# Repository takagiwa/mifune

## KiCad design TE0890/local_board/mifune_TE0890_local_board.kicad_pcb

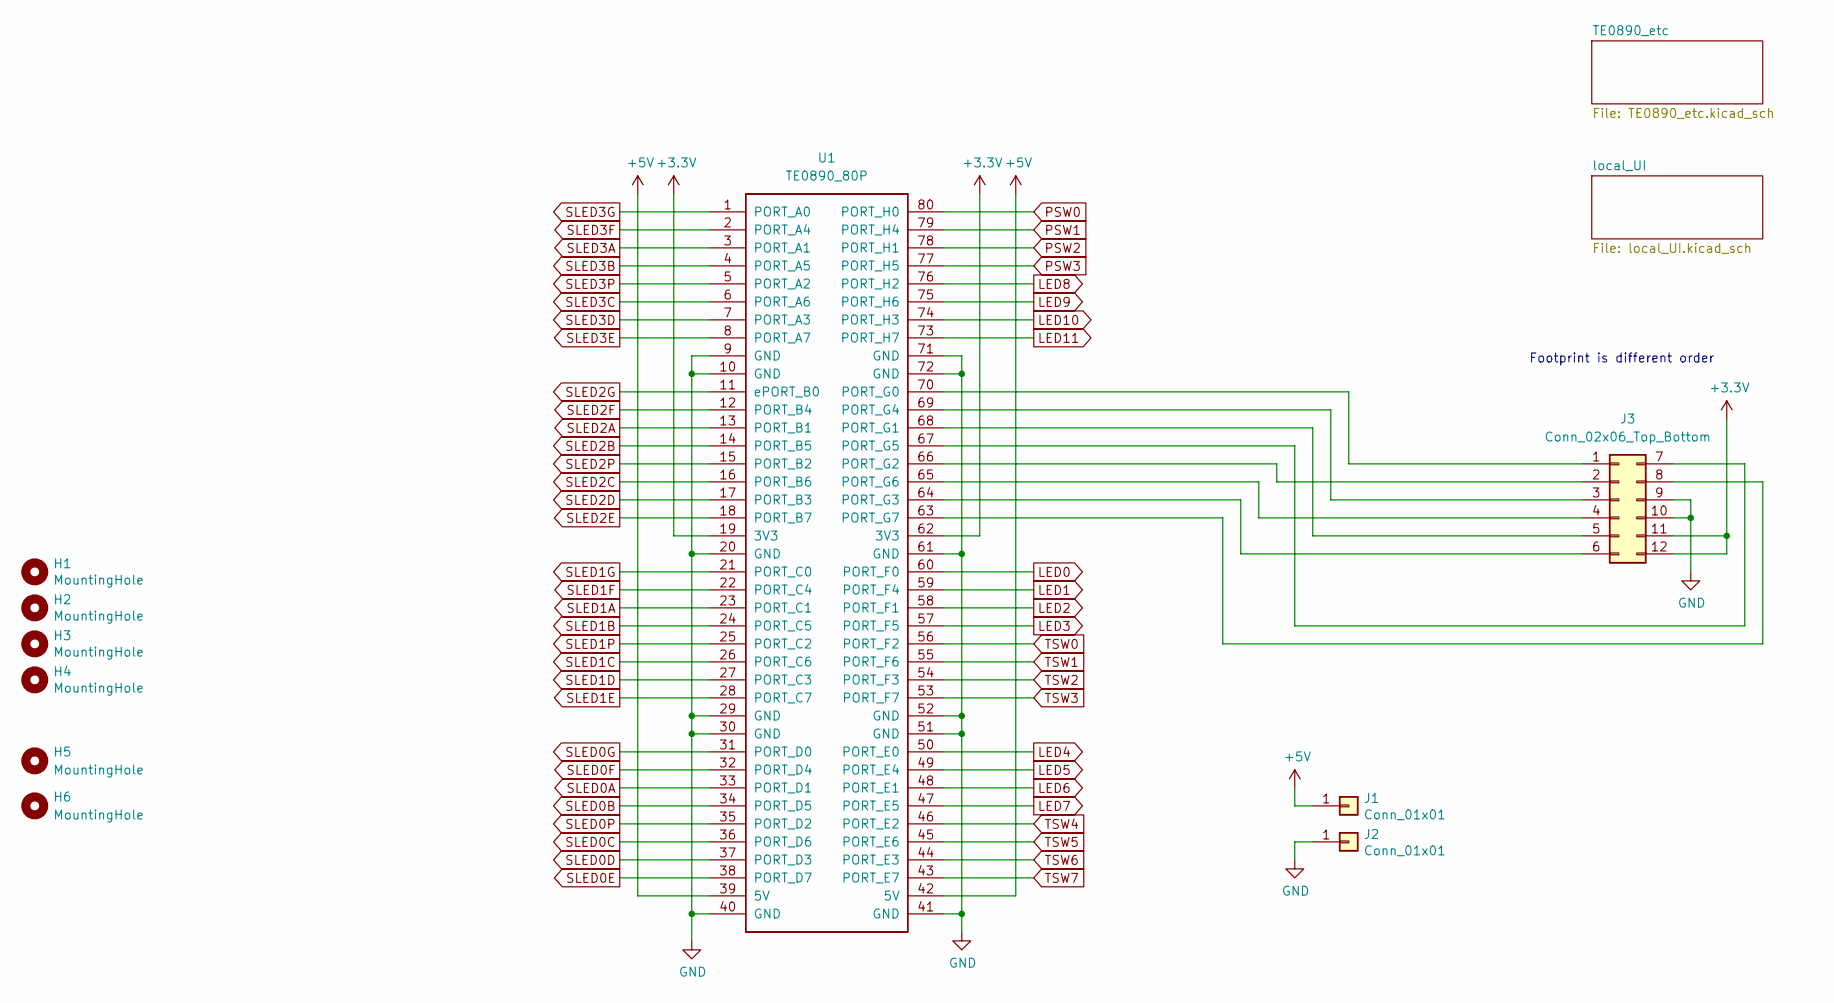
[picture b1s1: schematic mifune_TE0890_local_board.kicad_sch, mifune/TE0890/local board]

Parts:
H1, H2, H3, H4: MountingHole; MountingHole_3.2mm_M3
H5, H6: MountingHole; MountingHole_3.5mm
J1, J2: Conn_01x01; TestPoint_THTPad_D1.5mm_Drill0.7mm
J3: Conn_02x06_Top_Bottom; PinSocket_2x06_P2.54mm_Vertical
U1: TE0890_80P; TE0890_80pin

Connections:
+3V3: J3.11, J3.12, U1.19 (3V3), U1.62 (3V3); also elsewhere on the board
+5V: J1.1, U1.39 (5V), U1.42 (5V); also elsewhere on the board
GND: J2.1, J3.9, J3.10, U1.9 (GND), U1.10 (GND), U1.20 (GND), U1.29 (GND), U1.30 (GND), U1.40 (GND), U1.41 (GND), U1.51 (GND), U1.52 (GND), U1.61 (GND), U1.71 (GND), U1.72 (GND); also elsewhere on the board
LED0: U1.60 (PORT_F0); also elsewhere on the board
LED1: U1.59 (PORT_F4); also elsewhere on the board
LED2: U1.58 (PORT_F1); also elsewhere on the board
LED3: U1.57 (PORT_F5); also elsewhere on the board
LED4: U1.50 (PORT_E0); also elsewhere on the board
LED5: U1.49 (PORT_E4); also elsewhere on the board
LED6: U1.48 (PORT_E1); also elsewhere on the board
LED7: U1.47 (PORT_E5); also elsewhere on the board
LED8: U1.76 (PORT_H2); also elsewhere on the board
LED9: U1.75 (PORT_H6); also elsewhere on the board
LED10: U1.74 (PORT_H3); also elsewhere on the board
LED11: U1.73 (PORT_H7); also elsewhere on the board
unnamed: J3.1, U1.70 (PORT_G0)
unnamed: J3.2, U1.66 (PORT_G2)
unnamed: J3.3, U1.69 (PORT_G4)
unnamed: J3.4, U1.65 (PORT_G6)
unnamed: J3.5, U1.68 (PORT_G1)
unnamed: J3.6, U1.64 (PORT_G3)
unnamed: J3.7, U1.67 (PORT_G5)
unnamed: J3.8, U1.63 (PORT_G7)
PSW0: U1.80 (PORT_H0); also elsewhere on the board
PSW1: U1.79 (PORT_H4); also elsewhere on the board
PSW2: U1.78 (PORT_H1); also elsewhere on the board
PSW3: U1.77 (PORT_H5); also elsewhere on the board
SLED0A: U1.33 (PORT_D1); also elsewhere on the board
SLED0B: U1.34 (PORT_D5); also elsewhere on the board
SLED0C: U1.36 (PORT_D6); also elsewhere on the board
SLED0D: U1.37 (PORT_D3); also elsewhere on the board
SLED0E: U1.38 (PORT_D7); also elsewhere on the board
SLED0F: U1.32 (PORT_D4); also elsewhere on the board
SLED0G: U1.31 (PORT_D0); also elsewhere on the board
SLED0P: U1.35 (PORT_D2); also elsewhere on the board
SLED1A: U1.23 (PORT_C1); also elsewhere on the board
SLED1B: U1.24 (PORT_C5); also elsewhere on the board
SLED1C: U1.26 (PORT_C6); also elsewhere on the board
SLED1D: U1.27 (PORT_C3); also elsewhere on the board
SLED1E: U1.28 (PORT_C7); also elsewhere on the board
SLED1F: U1.22 (PORT_C4); also elsewhere on the board
SLED1G: U1.21 (PORT_C0); also elsewhere on the board
SLED1P: U1.25 (PORT_C2); also elsewhere on the board
SLED2A: U1.13 (PORT_B1); also elsewhere on the board
SLED2B: U1.14 (PORT_B5); also elsewhere on the board
SLED2C: U1.16 (PORT_B6); also elsewhere on the board
SLED2D: U1.17 (PORT_B3); also elsewhere on the board
SLED2E: U1.18 (PORT_B7); also elsewhere on the board
SLED2F: U1.12 (PORT_B4); also elsewhere on the board
SLED2G: U1.11 (ePORT_B0); also elsewhere on the board
SLED2P: U1.15 (PORT_B2); also elsewhere on the board
SLED3A: U1.3 (PORT_A1); also elsewhere on the board
SLED3B: U1.4 (PORT_A5); also elsewhere on the board
SLED3C: U1.6 (PORT_A6); also elsewhere on the board
SLED3D: U1.7 (PORT_A3); also elsewhere on the board
SLED3E: U1.8 (PORT_A7); also elsewhere on the board
SLED3F: U1.2 (PORT_A4); also elsewhere on the board
SLED3G: U1.1 (PORT_A0); also elsewhere on the board
SLED3P: U1.5 (PORT_A2); also elsewhere on the board
TSW0: U1.56 (PORT_F2); also elsewhere on the board
TSW1: U1.55 (PORT_F6); also elsewhere on the board
TSW2: U1.54 (PORT_F3); also elsewhere on the board
TSW3: U1.53 (PORT_F7); also elsewhere on the board
TSW4: U1.46 (PORT_E2); also elsewhere on the board
TSW5: U1.45 (PORT_E6); also elsewhere on the board
TSW6: U1.44 (PORT_E3); also elsewhere on the board
TSW7: U1.43 (PORT_E7); also elsewhere on the board

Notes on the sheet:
Footprint is different order

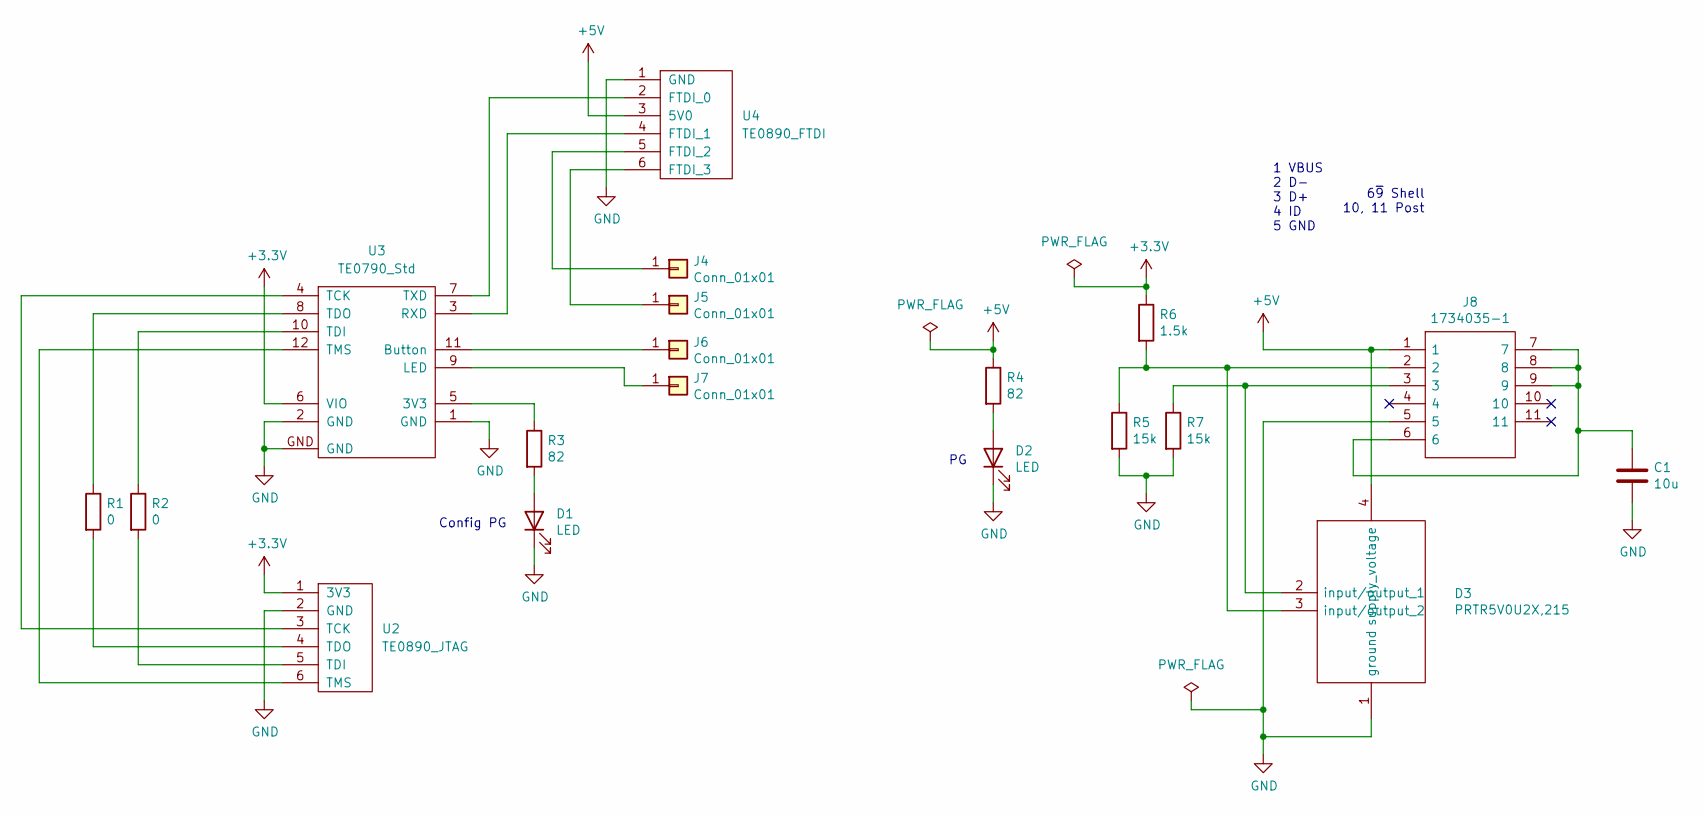
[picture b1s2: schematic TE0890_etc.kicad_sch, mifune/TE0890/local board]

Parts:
C1: 10u; C_0805_2012Metric_Pad1.18x1.45mm_HandSolder
D1, D2: LED; LED_1206_3216Metric_Pad1.42x1.75mm_HandSolder
D3: PRTR5V0U2X,215; PRTR5V0U2X; Mouser Part Number 771-PRTR5V0U2X-T/R
J4, J5, J6, J7: Conn_01x01; TestPoint_THTPad_D2.0mm_Drill1.0mm
J8: 1734035-1; 17340351; Mouser Part Number 571-1734035-1
R1, R2: 0; R_0805_2012Metric_Pad1.20x1.40mm_HandSolder
R3, R4: 82; R_0805_2012Metric_Pad1.20x1.40mm_HandSolder
R5, R7: 15k; R_0805_2012Metric_Pad1.20x1.40mm_HandSolder
R6: 1.5k; R_0805_2012Metric_Pad1.20x1.40mm_HandSolder
U2: TE0890_JTAG; PinHeader_1x06_P2.54mm_Vertical
U3: TE0790_Std; TE0790
U4: TE0890_FTDI; PinHeader_1x06_P2.54mm_Vertical

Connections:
+3V3: R6.1, U2.1 (3V3), U3.6 (VIO); also elsewhere on the board
+5V: D3.4 (supply_voltage), J8.1, R4.1, U4.3 (5V0); also elsewhere on the board
GND: C1.2, D1.1 (K), D2.1 (K), D3.1 (ground), J8.5, R5.2, R7.2, U2.2 (GND), U3.1 (GND), U3.2 (GND), U3.GND, U4.1 (GND); also elsewhere on the board
unnamed: C1.1, J8.6, J8.7, J8.8, J8.9
unnamed: D1.2 (A), R3.2
unnamed: D2.2 (A), R4.2
unnamed: D3.2 (input/output_1), J8.3, R7.1
unnamed: D3.3 (input/output_2), J8.2, R5.1, R6.2
unnamed: J4.1, U4.5 (FTDI_2)
unnamed: J5.1, U4.6 (FTDI_3)
unnamed: J6.1, U3.11 (Button)
unnamed: J7.1, U3.9 (LED)
unnamed: R1.1, U3.8 (TDO)
unnamed: R1.2, U2.4 (TDO)
unnamed: R2.1, U3.10 (TDI)
unnamed: R2.2, U2.5 (TDI)
unnamed: R3.1, U3.5 (3V3)
unnamed: U2.3 (TCK), U3.4 (TCK)
unnamed: U2.6 (TMS), U3.12 (TMS)
unnamed: U3.3 (RXD), U4.4 (FTDI_1)
unnamed: U3.7 (TXD), U4.2 (FTDI_0)

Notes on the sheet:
Config PG
6~{9} Shell 10, 11 Post
1 VBUS 2 D- 3 D+ 4 ID 5 GND

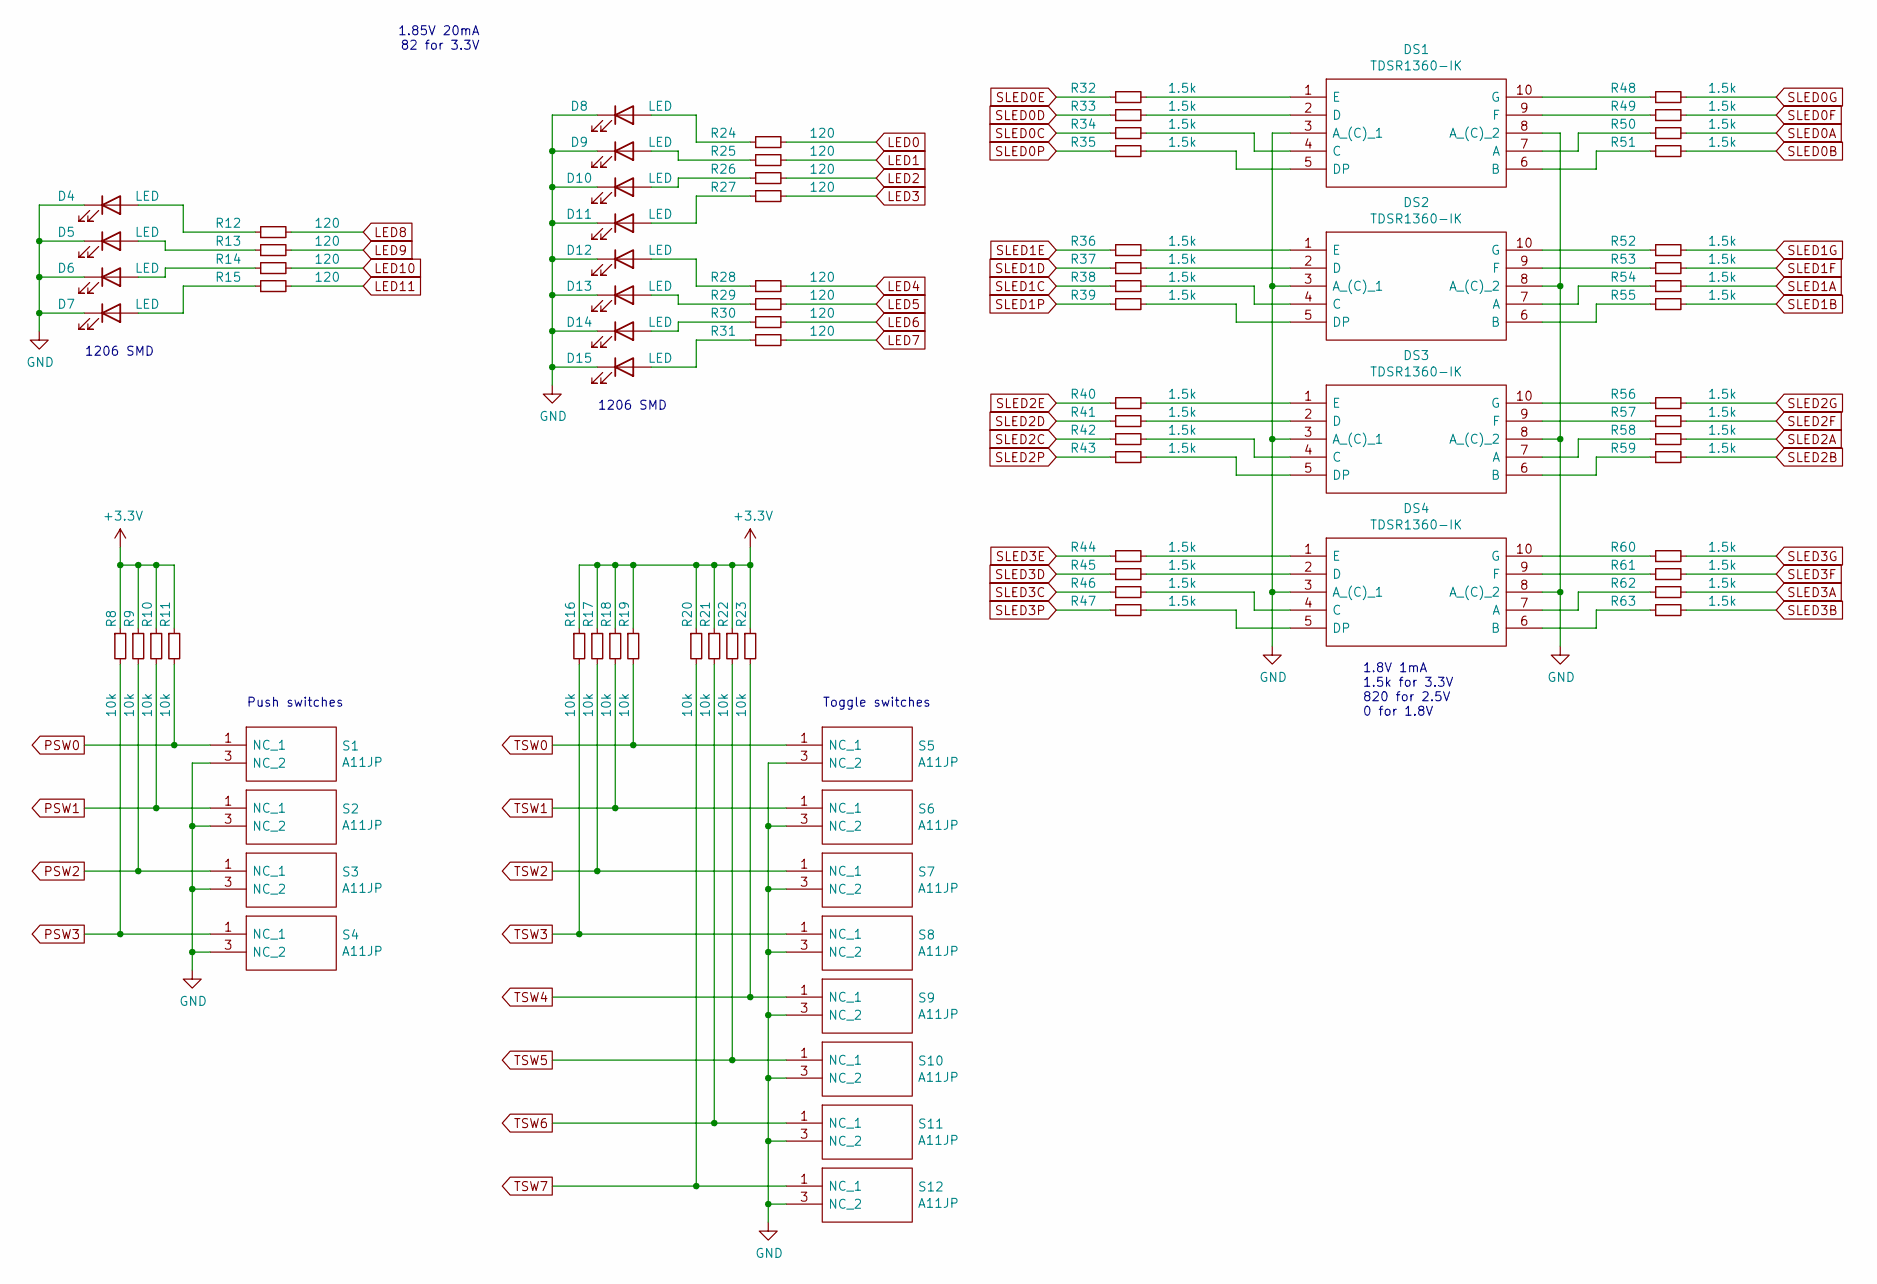
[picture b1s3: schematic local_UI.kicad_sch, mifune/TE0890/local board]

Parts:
D4, D5, D6, D7, D8, D9, D10, D11, D12, D13, D14, D15: LED; LED_1206_3216Metric_Pad1.42x1.75mm_HandSolder
DS1, DS2, DS3, DS4: TDSR1360-IK; TDSR1360IK; Mouser Part Number 78-TDSR1360-IK
R8, R9, R10, R11, R16, R17, R18, R19, R20, R21, R22, R23: 10k; R_0805_2012Metric_Pad1.20x1.40mm_HandSolder
R12, R13, R14, R15, R24, R25, R26, R27, R28, R29, R30, R31: 120; R_0805_2012Metric_Pad1.20x1.40mm_HandSolder
R32, R33, R34, R35, R36, R37, R38, R39, R40, R41, R42, R43, R44, R45, R46, R47, R48, R49, R50, R51, R52, R53, R54, R55, R56, R57, R58, R59, R60, R61, R62, R63: 1.5k; R_0805_2012Metric_Pad1.20x1.40mm_HandSolder
S1, S2, S3, S4, S5, S6, S7, S8, S9, S10, S11, S12: A11JP; Mouser Part Number 633-A11JP

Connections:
+3V3: R8.1, R9.1, R10.1, R11.1, R16.1, R17.1, R18.1, R19.1, R20.1, R21.1, R22.1, R23.1; also elsewhere on the board
GND: D4.1 (K), D5.1 (K), D6.1 (K), D7.1 (K), D8.1 (K), D9.1 (K), D10.1 (K), D11.1 (K), D12.1 (K), D13.1 (K), D14.1 (K), D15.1 (K), DS1.3 (A_(C)_1), DS1.8 (A_(C)_2), DS2.3 (A_(C)_1), DS2.8 (A_(C)_2), DS3.3 (A_(C)_1), DS3.8 (A_(C)_2), DS4.3 (A_(C)_1), DS4.8 (A_(C)_2), S1.3 (NC_2), S2.3 (NC_2), S3.3 (NC_2), S4.3 (NC_2), S5.3 (NC_2), S6.3 (NC_2), S7.3 (NC_2), S8.3 (NC_2), S9.3 (NC_2), S10.3 (NC_2), S11.3 (NC_2), S12.3 (NC_2); also elsewhere on the board
LED0: R24.2; also elsewhere on the board
LED1: R25.2; also elsewhere on the board
LED2: R26.2; also elsewhere on the board
LED3: R27.2; also elsewhere on the board
LED4: R28.2; also elsewhere on the board
LED5: R29.2; also elsewhere on the board
LED6: R30.2; also elsewhere on the board
LED7: R31.2; also elsewhere on the board
LED8: R12.2; also elsewhere on the board
LED9: R13.2; also elsewhere on the board
LED10: R14.2; also elsewhere on the board
LED11: R15.2; also elsewhere on the board
unnamed: D4.2 (A), R12.1
unnamed: D5.2 (A), R13.1
unnamed: D6.2 (A), R14.1
unnamed: D7.2 (A), R15.1
unnamed: D8.2 (A), R24.1
unnamed: D9.2 (A), R25.1
unnamed: D10.2 (A), R26.1
unnamed: D11.2 (A), R27.1
unnamed: D12.2 (A), R28.1
unnamed: D13.2 (A), R29.1
unnamed: D14.2 (A), R30.1
unnamed: D15.2 (A), R31.1
unnamed: DS1.1 (E), R32.2
unnamed: DS1.2 (D), R33.2
unnamed: DS1.4 (C), R34.2
unnamed: DS1.5 (DP), R35.2
unnamed: DS1.6 (B), R51.1
unnamed: DS1.7 (A), R50.1
unnamed: DS1.9 (F), R49.1
unnamed: DS1.10 (G), R48.1
unnamed: DS2.1 (E), R36.2
unnamed: DS2.2 (D), R37.2
unnamed: DS2.4 (C), R38.2
unnamed: DS2.5 (DP), R39.2
unnamed: DS2.6 (B), R55.1
unnamed: DS2.7 (A), R54.1
unnamed: DS2.9 (F), R53.1
unnamed: DS2.10 (G), R52.1
unnamed: DS3.1 (E), R40.2
unnamed: DS3.2 (D), R41.2
unnamed: DS3.4 (C), R42.2
unnamed: DS3.5 (DP), R43.2
unnamed: DS3.6 (B), R59.1
unnamed: DS3.7 (A), R58.1
unnamed: DS3.9 (F), R57.1
unnamed: DS3.10 (G), R56.1
unnamed: DS4.1 (E), R44.2
unnamed: DS4.2 (D), R45.2
unnamed: DS4.4 (C), R46.2
unnamed: DS4.5 (DP), R47.2
unnamed: DS4.6 (B), R63.1
unnamed: DS4.7 (A), R62.1
unnamed: DS4.9 (F), R61.1
unnamed: DS4.10 (G), R60.1
PSW0: R11.2, S1.1 (NC_1); also elsewhere on the board
PSW1: R10.2, S2.1 (NC_1); also elsewhere on the board
PSW2: R9.2, S3.1 (NC_1); also elsewhere on the board
PSW3: R8.2, S4.1 (NC_1); also elsewhere on the board
SLED0A: R50.2; also elsewhere on the board
SLED0B: R51.2; also elsewhere on the board
SLED0C: R34.1; also elsewhere on the board
SLED0D: R33.1; also elsewhere on the board
SLED0E: R32.1; also elsewhere on the board
SLED0F: R49.2; also elsewhere on the board
SLED0G: R48.2; also elsewhere on the board
SLED0P: R35.1; also elsewhere on the board
SLED1A: R54.2; also elsewhere on the board
SLED1B: R55.2; also elsewhere on the board
SLED1C: R38.1; also elsewhere on the board
SLED1D: R37.1; also elsewhere on the board
SLED1E: R36.1; also elsewhere on the board
SLED1F: R53.2; also elsewhere on the board
SLED1G: R52.2; also elsewhere on the board
SLED1P: R39.1; also elsewhere on the board
SLED2A: R58.2; also elsewhere on the board
SLED2B: R59.2; also elsewhere on the board
SLED2C: R42.1; also elsewhere on the board
SLED2D: R41.1; also elsewhere on the board
SLED2E: R40.1; also elsewhere on the board
SLED2F: R57.2; also elsewhere on the board
SLED2G: R56.2; also elsewhere on the board
SLED2P: R43.1; also elsewhere on the board
SLED3A: R62.2; also elsewhere on the board
SLED3B: R63.2; also elsewhere on the board
SLED3C: R46.1; also elsewhere on the board
SLED3D: R45.1; also elsewhere on the board
SLED3E: R44.1; also elsewhere on the board
SLED3F: R61.2; also elsewhere on the board
SLED3G: R60.2; also elsewhere on the board
SLED3P: R47.1; also elsewhere on the board
TSW0: R19.2, S5.1 (NC_1); also elsewhere on the board
TSW1: R18.2, S6.1 (NC_1); also elsewhere on the board
TSW2: R17.2, S7.1 (NC_1); also elsewhere on the board
TSW3: R16.2, S8.1 (NC_1); also elsewhere on the board
TSW4: R23.2, S9.1 (NC_1); also elsewhere on the board
TSW5: R22.2, S10.1 (NC_1); also elsewhere on the board
TSW6: R21.2, S11.1 (NC_1); also elsewhere on the board
TSW7: R20.2, S12.1 (NC_1); also elsewhere on the board

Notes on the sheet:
Toggle switches
1206 SMD
1.8V 1mA 1.5k for 3.3V 820 for 2.5V 0 for 1.8V
Push switches
1.85V 20mA 82 for 3.3V

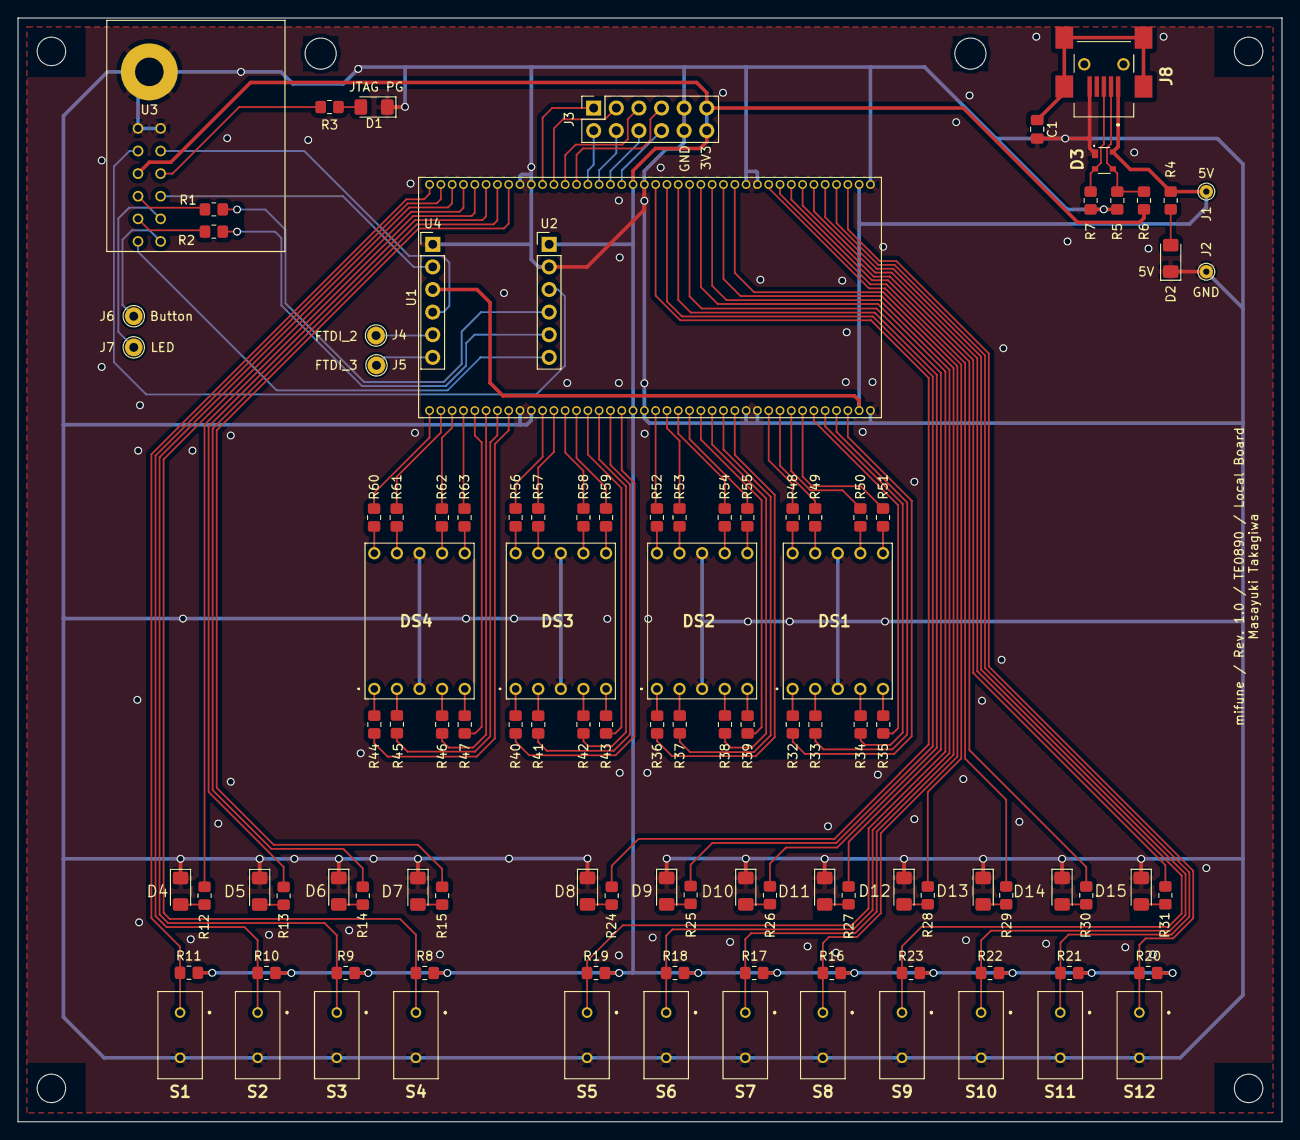
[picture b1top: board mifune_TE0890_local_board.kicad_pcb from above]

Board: 2 copper layers, 142.0 x 124.0 mm, 113 parts (0 on the bottom side), 129 nets.

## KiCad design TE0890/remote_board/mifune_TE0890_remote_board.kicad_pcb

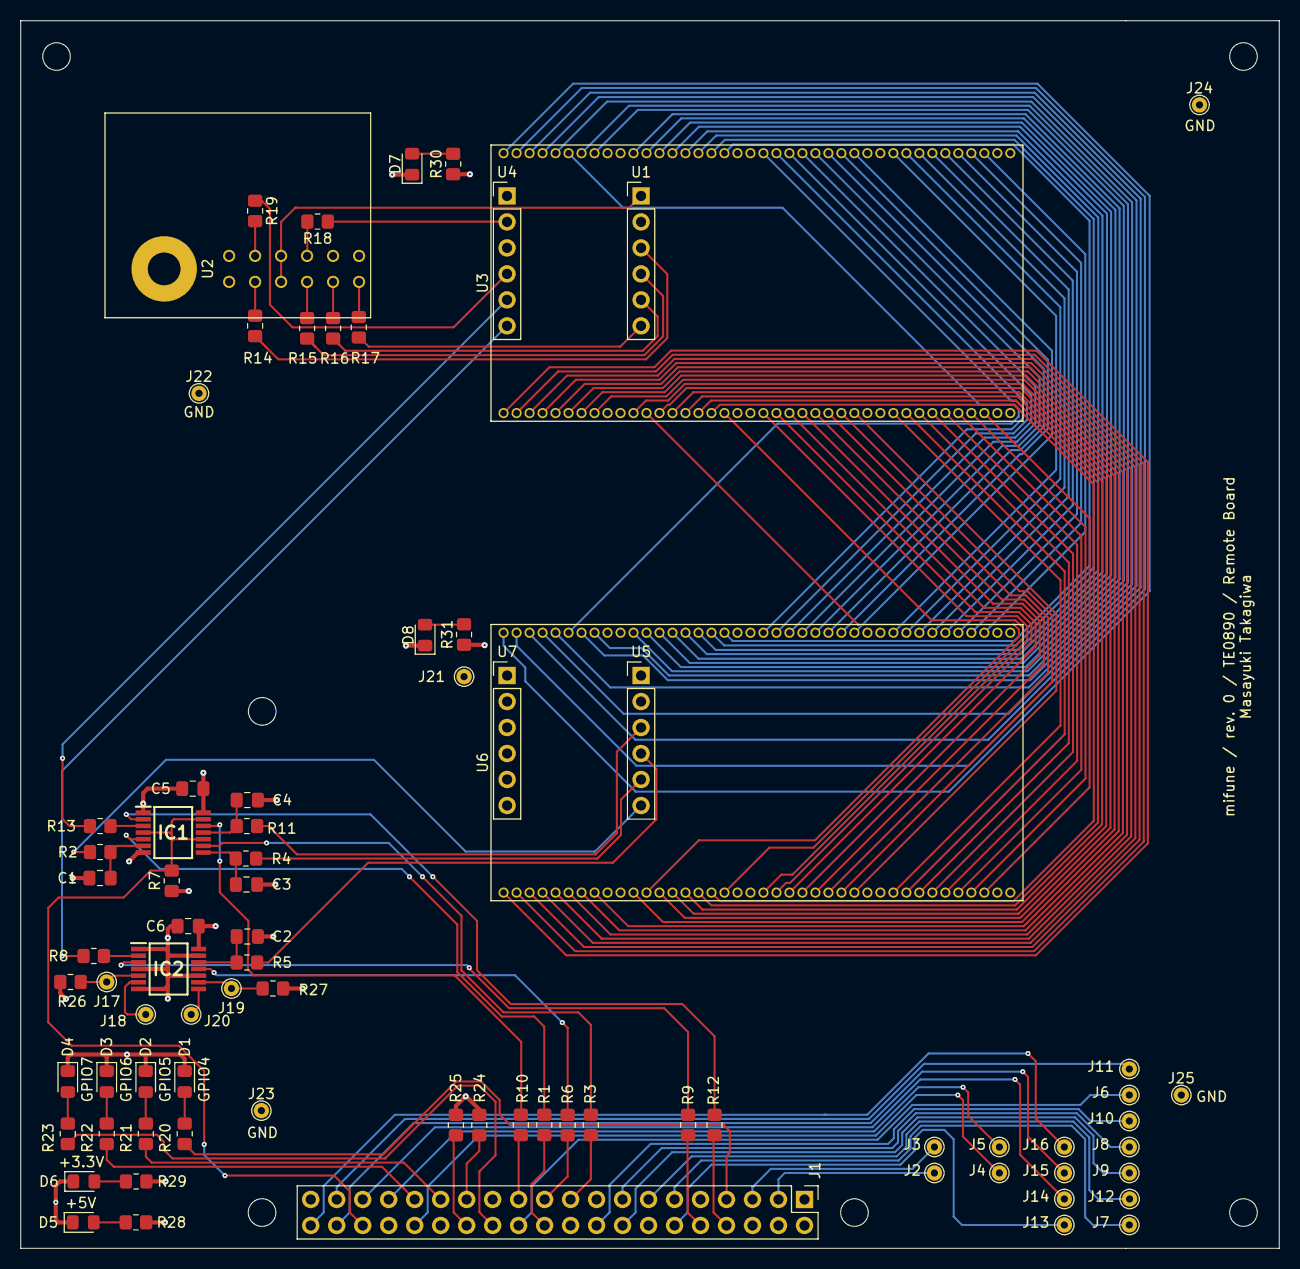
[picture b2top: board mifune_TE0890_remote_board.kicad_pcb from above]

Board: 4 copper layers, 123.0 x 120.0 mm, 85 parts (0 on the bottom side), 141 nets.

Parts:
C1, C2, C3, C4: 100p; C_0805_2012Metric_Pad1.18x1.45mm_HandSolder
C5, C6: 0.1u; C_0805_2012Metric_Pad1.18x1.45mm_HandSolder
D1, D2, D3, D4, D5, D6, D7, D8: LED; LED_0805_2012Metric_Pad1.15x1.40mm_HandSolder
H1, H2, H3, H4, H5, H6: MountingHole; MountingHole_2.7mm_M2.5
IC1, IC2: SN74LV4T125PWR; SOP65P640X120-14N
J1: Raspberry_Pi_2_3; PinHeader_2x20_P2.54mm_Vertical
J2, J3, J4, J5, J6, J7, J8, J9, J10, J11, J12, J13, J14, J15, J16, J17, J18, J19, J20, J22, J23, J24, J25: Conn_01x01; TestPoint_THTPad_D1.5mm_Drill0.7mm
J21: Conn_01x06; TestPoint_THTPad_D1.5mm_Drill0.7mm
R1, R3, R6, R8, R9, R10, R12, R13, R14, R15, R16, R17, R18, R19: 0; R_0805_2012Metric_Pad1.20x1.40mm_HandSolder
R2, R4, R5, R11: 100; R_0805_2012Metric_Pad1.20x1.40mm_HandSolder
R7: 4.7k; R_0805_2012Metric_Pad1.20x1.40mm_HandSolder
R20, R21, R22, R23, R29, R30, R31: 820; R_0805_2012Metric_Pad1.20x1.40mm_HandSolder
R24, R25, R26, R27, R28: 3.9k; R_0805_2012Metric_Pad1.20x1.40mm_HandSolder
U1, U5: TE0890_JTAG; PinHeader_1x06_P2.54mm_Vertical
U2: TE0790_Std; TE0790
U3, U6: TE0890_80P; TE0890_80pin
U4, U7: TE0890_FTDI; PinHeader_1x06_P2.54mm_Vertical

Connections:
+3.3VA: C5.1, IC1.14, R31.1, U5.1, U6.19, U6.62
+3.3VP: R30.1, U3.19, U3.62
+3V3: C6.1, IC2.14, J1.1, J1.17, R7.1, R24.1, R25.1, R26.2, R27.1, R29.1
+5V: J1.2, J1.4, R28.1, U3.39, U3.42, U4.3, U6.39, U6.42
/GPIO4: J1.7, R20.1
/GPIO5: J1.29, R21.1
/GPIO6: J1.31, R22.1
/GPIO7: J1.26, R23.1
/GPIO8: J1.24, J6.1
/GPIO17: J1.11, J7.1
/GPIO22: J1.15, J8.1
/GPIO23: J1.16, J9.1
/GPIO24: J1.18, J10.1
/GPIO26: J1.37, J11.1
/GPIO27: J1.13, J12.1
/PI_JTAG_OE: IC1.4, IC1.10, IC1.13, J1.36, R7.2
/PI_JTAG_TCK_SRC: J1.23, R10.1
/PI_JTAG_TDI_SRC: J1.19, R3.1
/PI_JTAG_TDO_DST: J1.21, R6.1
/PI_JTAG_TMS_SRC: J1.22, R1.2
/PI_RXD_DST: J1.10, R9.2
/PI_TXD_SRC: J1.8, R12.2
/PWM0: J1.32, J4.1
/PWM1: J1.33, J5.1
/SCL: J1.5, J3.1
/SDA: J1.3, J2.1
/SPI_CE0: J1.12, J13.1
/SPI_MISO: J1.35, J14.1
/SPI_MOSI: J1.38, J15.1
/SPI_SCLK: J1.40, J16.1
GND: C1.2, C2.2, C3.2, C4.2, C5.2, C6.2, D1.1, D2.1, D3.1, D4.1, D5.1, D6.1, D7.1, D8.1, IC1.1, IC1.7, IC2.1, IC2.4, IC2.7, IC2.10, IC2.13, J1.6, J1.9, J1.14, J1.20, J1.25, J1.30, J1.34, J1.39, J22.1, J23.1, J24.1, J25.1, U1.2, U2.1, U2.2, U2.GND, U3.9, U3.10, U3.20, U3.29, U3.30, U3.40, U3.41, U3.51, U3.52, U3.61, U3.71, U3.72, U4.1, U5.2, U6.9, U6.10, U6.20, U6.29, U6.30, U6.40, U6.41, U6.51, U6.52, U6.61, U6.71, U6.72
unnamed: C1.1, IC1.6, R2.1
unnamed: C2.1, IC2.12, R5.2
unnamed: C3.1, IC1.8, R4.2
unnamed: C4.1, IC1.11, R11.2
unnamed: D1.2, R20.2
unnamed: D2.2, R21.2
unnamed: D3.2, R22.2
unnamed: D4.2, R23.2
unnamed: D5.2, R28.2
unnamed: D6.2, R29.2
unnamed: D7.2, R30.2
unnamed: D8.2, R31.2
unnamed: IC1.2, R12.1
unnamed: IC1.3, R13.1
unnamed: IC1.5, R1.1
unnamed: IC1.9, R3.2
unnamed: IC1.12, R10.2
unnamed: IC2.2, R8.1
unnamed: IC2.3, R9.1
unnamed: IC2.5, J17.1, R26.1
unnamed: IC2.6, J18.1
unnamed: IC2.8, J20.1
unnamed: IC2.9, J19.1, R27.2
unnamed: IC2.11, R6.2
unnamed: J1.27, R24.2
unnamed: J1.28, R25.2
unnamed: J21.1, U7.1
unnamed: R14.1, U2.4
unnamed: R14.2, U1.3
unnamed: R15.1, U2.8
unnamed: R15.2, U1.4
unnamed: R16.1, U2.10
unnamed: R16.2, U1.5
unnamed: R17.1, U2.12
unnamed: R17.2, U1.6
unnamed: R18.1, U4.2
unnamed: R18.2, U2.7
unnamed: R19.1, U4.4
unnamed: R19.2, U2.3
unnamed: U1.1, U2.5, U2.6
PI_JTAG_TCK: R11.1, U5.3
PI_JTAG_TDI: R4.1, U5.5
PI_JTAG_TDO: R5.1, U5.4
PI_JTAG_TMS: R2.2, U5.6
PI_RXD: R8.2, U4.6
PI_TXD: R13.2, U4.5
PORT_A0: U3.1, U6.1
PORT_A1: U3.3, U6.3
PORT_A2: U3.5, U6.5
PORT_A3: U3.7, U6.7
PORT_A4: U3.2, U6.2
PORT_A5: U3.4, U6.4
PORT_A6: U3.6, U6.6
PORT_A7: U3.8, U6.8
PORT_B0: U3.11, U6.11
PORT_B1: U3.13, U6.13
PORT_B2: U3.15, U6.15
PORT_B3: U3.17, U6.17
PORT_B4: U3.12, U6.12
PORT_B5: U3.14, U6.14
PORT_B6: U3.16, U6.16
PORT_B7: U3.18, U6.18
PORT_C0: U3.21, U6.21
PORT_C1: U3.23, U6.23
PORT_C2: U3.25, U6.25
PORT_C3: U3.27, U6.27
PORT_C4: U3.22, U6.22
PORT_C5: U3.24, U6.24
PORT_C6: U3.26, U6.26
PORT_C7: U3.28, U6.28
PORT_D0: U3.31, U6.31
PORT_D1: U3.33, U6.33
PORT_D2: U3.35, U6.35
PORT_D3: U3.37, U6.37
PORT_D4: U3.32, U6.32
PORT_D5: U3.34, U6.34
PORT_D6: U3.36, U6.36
PORT_D7: U3.38, U6.38
PORT_E0: U3.50, U6.50
PORT_E1: U3.48, U6.48
PORT_E2: U3.46, U6.46
PORT_E3: U3.44, U6.44
PORT_E4: U3.49, U6.49
PORT_E5: U3.47, U6.47
PORT_E6: U3.45, U6.45
PORT_E7: U3.43, U6.43
PORT_F0: U3.60, U6.60
PORT_F1: U3.58, U6.58
PORT_F2: U3.56, U6.56
PORT_F3: U3.54, U6.54
PORT_F4: U3.59, U6.59
PORT_F5: U3.57, U6.57
PORT_F6: U3.55, U6.55
PORT_F7: U3.53, U6.53
PORT_G0: U3.70, U6.70
PORT_G1: U3.68, U6.68
PORT_G2: U3.66, U6.66
PORT_G3: U3.64, U6.64
PORT_G4: U3.69, U6.69
PORT_G5: U3.67, U6.67
PORT_G6: U3.65, U6.65
PORT_G7: U3.63, U6.63
PORT_H0: U3.80, U6.80
PORT_H1: U3.78, U6.78
PORT_H2: U3.76, U6.76
PORT_H3: U3.74, U6.74
PORT_H4: U3.79, U6.79
PORT_H5: U3.77, U6.77
PORT_H6: U3.75, U6.75
PORT_H7: U3.73, U6.73

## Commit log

2020-10-04 Work in progress
2021-01-01 First prototype
2021-02-13 両面基板の作業途中。
2021-04-20 remote board 2021 March 07
2022-03-21 local board rev.1.0 work in progress
2023-02-28 local board refine

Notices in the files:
TE0890/local_board/TE0890_etc.kicad_sch:
GPLv2
